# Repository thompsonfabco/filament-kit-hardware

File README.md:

If you enjoy what I do, consider supporting me! Every little bit means the world! https://ko-fi.com/thompsonfabco

# filament-kit-hardware

Hardware designs for the peripheral devices of [filament-kit](https://github.com/thompsonfabco/filament-kit): the
standard they share, build guides, wiring, parts, enclosures and bench results.

Firmware and the station code that talks to these devices live in filament-kit, not here.

## Devices

| Device | What it is | Status |
|---|---|---|
| [`intake-panel`](devices/intake-panel/guide.md) | Illuminated buttons (LEDs), OLED, speaker and room-air sensor for the intake station | ESP32-C3 (kit firmware 11); two board designs, a DIY through-hole board and a JLCPCB board |
| [Printer station (`printer-station`)](devices/printer-station/guide.md) | NFC reader with a knob that loads a spool into a printer slot | ESP32-C3; printer scan station case (Body, Face, Retainer and a 3MF print file) in `enclosures/printer-station/`, CC BY-NC-SA 4.0; fit unchecked |
| [`station-nfc`](devices/station-nfc/guide.md) | PN532 NFC reader on the intake station's USB | Bought (Teyleten PN532 V2.0, USB) |
| [`scale`](devices/scale/guide.md) | DYMO M10 USB postal scale | Bought; guide and parts list |
| [`webcam`](devices/webcam/guide.md) | USB camera that photographs new spools | Bought; guide and parts list |

The peripheral standard is in [standard.md](standard.md). The current design is
[specs/2026-11-09-peripheral-standard-design.md](specs/2026-11-09-peripheral-standard-design.md).

## Releases

Each release (a `vX.Y.Z` tag) carries the enclosure models from `enclosures/`:

- one zip per enclosure folder, `<device>-step-<version>.zip`, holding that folder's STEP files and the model `LICENSE` inside a folder named `<device>`;
- each print file (3MF), copied out as `<name>-<version>.3mf`.

Names are lowercase with hyphens. `python -I tools/make_release.py --version vX.Y.Z --out <dir>` builds the same files locally.

A tag `<group>-vX.Y` (for example `intake-station-v1.0`) releases one group: only the enclosure folders named `<group>` or `<group>-...` are built, and the version in the file names is the `vX.Y` part. Locally, add `--only <group>`.

## License

Everything outside `enclosures/` is licensed under GPL-3.0-only (see `LICENSE`), (c) 2026 thompsonfabco.

The model files in `enclosures/` are licensed under CC BY-NC-SA 4.0 (see `enclosures/LICENSE`). You are free to use, share and adapt them for any non-commercial purpose, with attribution, and adaptations must be shared under the same licence. No commercial use without permission.

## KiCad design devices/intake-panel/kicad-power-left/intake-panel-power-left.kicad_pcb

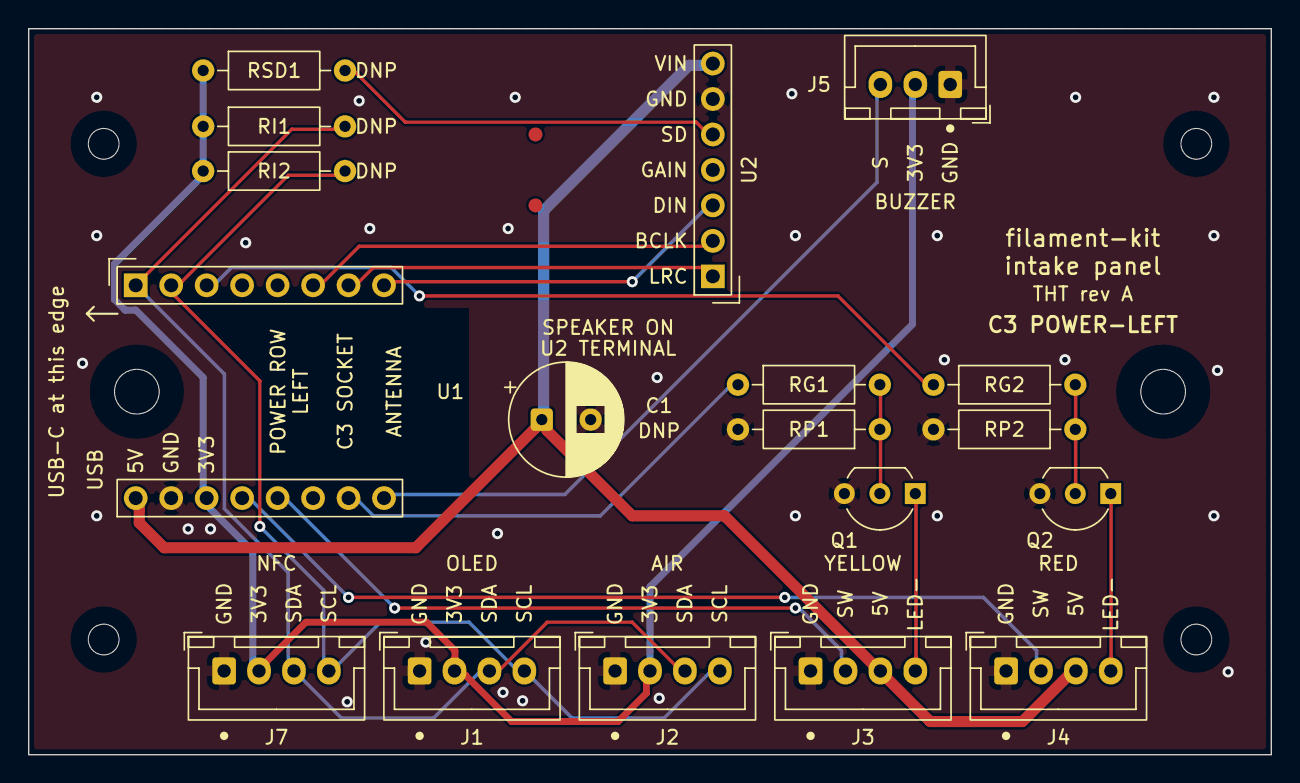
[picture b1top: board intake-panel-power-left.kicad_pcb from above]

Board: 2 copper layers, 89.0 x 52.0 mm, 19 parts (0 on the bottom side), 18 nets.

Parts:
C1: 470uF 10V; CP_Radial_D8.0mm_P3.50mm
J1: OLED; JST_XH_B4B-XH-A_1x04_P2.50mm_Vertical
J2: AIR; JST_XH_B4B-XH-A_1x04_P2.50mm_Vertical
J3: YELLOW; JST_XH_B4B-XH-A_1x04_P2.50mm_Vertical
J4: RED; JST_XH_B4B-XH-A_1x04_P2.50mm_Vertical
J5: BUZZER; JST_XH_B3B-XH-A_1x03_P2.50mm_Vertical
J7: NFC; JST_XH_B4B-XH-A_1x04_P2.50mm_Vertical
PCB1: ElectroCookie_Full
Q1, Q2: BS170; TO-92_Inline_Wide
RG1, RG2: 220; R_Axial_DIN0207_L6.3mm_D2.5mm_P10.16mm_Horizontal
RI1, RI2: 4.7k; R_Axial_DIN0207_L6.3mm_D2.5mm_P10.16mm_Horizontal
RP1, RP2: 100k; R_Axial_DIN0207_L6.3mm_D2.5mm_P10.16mm_Horizontal
RSD1: 10k; R_Axial_DIN0207_L6.3mm_D2.5mm_P10.16mm_Horizontal
U1: ESP32-C3 Super Mini; ESP32-C3_SuperMini_Socket_PowerLeft
U2: MAX98357 module; MAX98357_Module_Socket

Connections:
+3V3: J1.2, J2.2, J5.2, J7.2, RI1.1, RI2.1, RSD1.1, U1.11
+5V: C1.1, J3.3, J4.3, U1.9, U2.7
/AMP_SD: RSD1.2, U2.5
/BTN_DISCARD: J4.2, U1.12
/BTN_HOLD: J3.2, U1.13
/BUZZER: J5.3, U1.16
/DISCARD_LAMP-: J4.4, Q2.1
/HOLD_LAMP-: J3.4, Q1.1
/I2S_BCLK: U1.6, U2.2
/I2S_DIN: U1.8, U2.3
/I2S_LRC: U1.7, U2.1
/LAMP_DISCARD: RG2.1, U1.3
/LAMP_HOLD: RG1.1, U1.15
/Q1_G: Q1.2, RG1.2, RP1.1
/Q2_G: Q2.2, RG2.2, RP2.1
/SCL: J1.4, J2.4, J7.4, RI2.2, U1.2
/SDA: J1.3, J2.3, J7.3, RI1.2, U1.1
GND: C1.2, J1.1, J2.1, J3.1, J4.1, J5.1, J7.1, Q1.3, Q2.3, RP1.2, RP2.2, U1.10, U2.6

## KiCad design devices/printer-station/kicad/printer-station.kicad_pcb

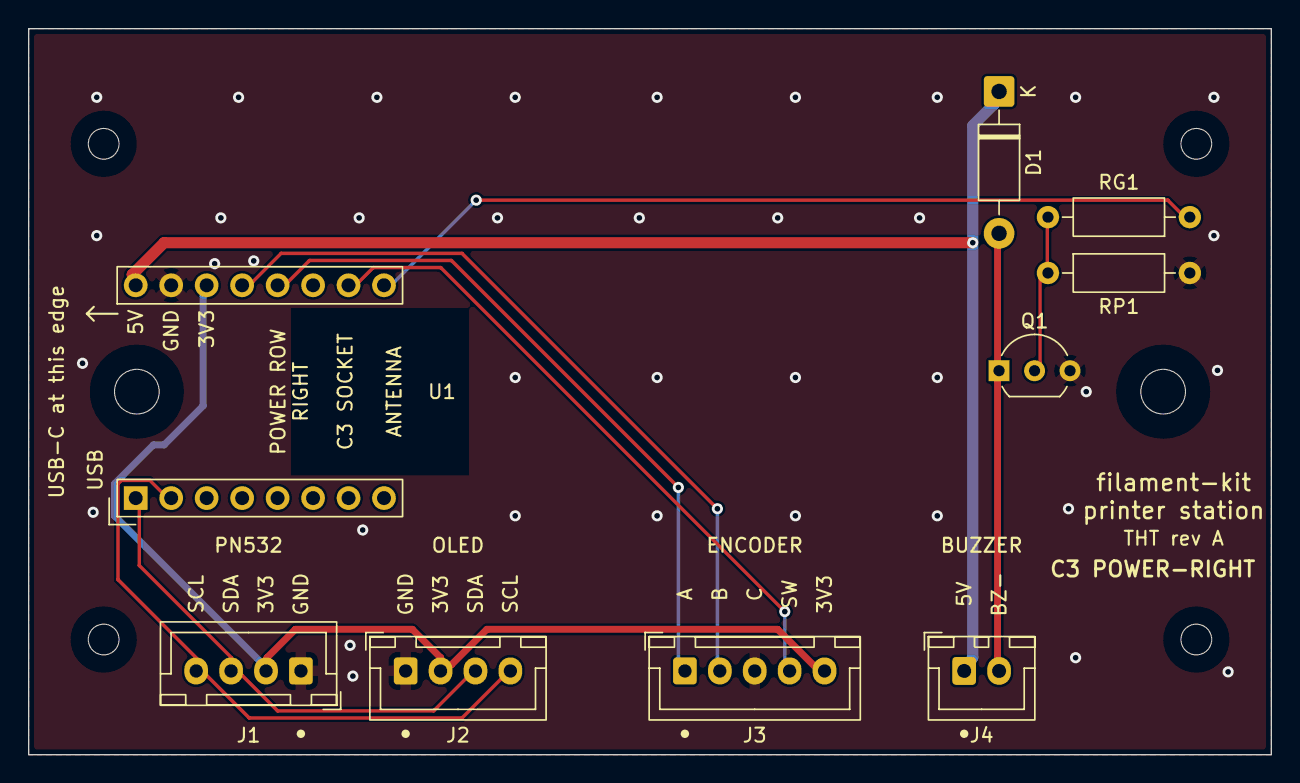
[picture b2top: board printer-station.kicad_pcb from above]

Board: 2 copper layers, 89.0 x 52.0 mm, 10 parts (0 on the bottom side), 11 nets.

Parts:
D1: 1N4001; D_DO-41_SOD81_P10.16mm_Horizontal
J1: PN532 XH-4; JST_XH_B4B-XH-A_1x04_P2.50mm_Vertical
J2: OLED XH-4; JST_XH_B4B-XH-A_1x04_P2.50mm_Vertical
J3: Encoder XH-5; JST_XH_B5B-XH-A_1x05_P2.50mm_Vertical
J4: Buzzer XH-2; JST_XH_B2B-XH-A_1x02_P2.50mm_Vertical
PCB1: ElectroCookie_Full
Q1: BS170; TO-92_Inline_Wide
RG1: 220; R_Axial_DIN0207_L6.3mm_D2.5mm_P10.16mm_Horizontal
RP1: 100k; R_Axial_DIN0207_L6.3mm_D2.5mm_P10.16mm_Horizontal
U1: ESP32-C3_SuperMini; ESP32-C3_SuperMini_Socket

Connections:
/3V3: J1.2, J2.2, J3.5, U1.11
/5V: D1.1, J4.1, U1.9
/BUZZER: RG1.1, U1.16
/BZ-: D1.2, J4.2, Q1.1
/BZ_G: Q1.2, RG1.2, RP1.1
/ENC_CLK: J3.1, U1.13
/ENC_DT: J3.2, U1.12
/ENC_SW: J3.4, U1.15
/GND: J1.1, J2.1, J3.3, Q1.3, RP1.2, U1.10
/SCL: J1.4, J2.4, U1.2
/SDA: J1.3, J2.3, U1.1

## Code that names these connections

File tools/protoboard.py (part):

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}
NET_TEXT = {
    "GND": "ground", "5V": "USB 5 V", "3V3": "3.3 V from the C3", "SDA": "I2C data, GPIO 5",
    "SCL": "I2C clock, GPIO 6", "ENC_CLK": "encoder A, GPIO 3", "ENC_DT": "encoder B, GPIO 4",
    "ENC_SW": "encoder switch, GPIO 1", "BUZZER": "buzzer drive, GPIO 0", "BZ_G": "Q1 gate",
    "BZ-": "buzzer \u2212 / Q1 drain",
    "+5V": "USB 5 V", "+3V3": "3.3 V from the C3", "I2S_BCLK": "amplifier bit clock, GPIO 10",
    "I2S_LRC": "amplifier word select, GPIO 20", "I2S_DIN": "amplifier data, GPIO 21",
    "AMP_SD": "amplifier SD (on/off)", "BTN_HOLD": "yellow button, GPIO 3", "BTN_DISCARD": "red button, GPIO 4",
    "LAMP_HOLD": "yellow lamp drive, GPIO 1", "LAMP_DISCARD": "red lamp drive, GPIO 7", "Q1_G": "Q1 gate",
    "Q2_G": "Q2 gate", "HOLD_LAMP-": "yellow lamp − / Q1 drain", "DISCARD_LAMP-": "red lamp − / Q2 drain",
}
RES_BANDS = {"220": ["#d62728", "#d62728", "#7f4f24", "#c9a227"],
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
